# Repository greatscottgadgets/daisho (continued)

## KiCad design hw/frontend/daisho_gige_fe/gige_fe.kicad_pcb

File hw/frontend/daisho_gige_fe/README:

Copyright 2014 Mike Kershaw, Michael Ossmann

These files are part of HackRF.

This is a free hardware design; you can redistribute it and/or modify
it under the terms of the GNU General Public License as published by
the Free Software Foundation; either version 2, or (at your option)
any later version.

This design is distributed in the hope that it will be useful,
but WITHOUT ANY WARRANTY; without even the implied warranty of
MERCHANTABILITY or FITNESS FOR A PARTICULAR PURPOSE.  See the
GNU General Public License for more details.

You should have received a copy of the GNU General Public License
along with this design; see the file COPYING.  If not, write to
the Free Software Foundation, Inc., 51 Franklin Street,
Boston, MA 02110-1301, USA.

hardware notes:

Schematic and layout files were designed in KiCad, an open source electronic
design automation package.

order of copper layers:
    Copper 1:  C1F (front)
    Copper 2:  C2
    Copper 3:  C3
    Copper 4:  C1B (back)

PCB description: 4 layer PCB 0.0646 in
    Copper       1:  1 oz copper (1.4 mil)
    Dielectric 1-2:  6.7 mil prepreg
    Copper       2:  0.5 oz copper (0.7 mil)
    Dielectric 2-3:  47 mil core
    Copper       3:  0.5 oz copper (0.7 mil)
    Dielectric 3-4:  6.7 mil prepreg
    Copper       4:  1 oz copper (1.4 mil)

FR408 or similar substrate with Er=3.66 (+/- 0.1)
double side solder mask green
double side silkscreen white
6 mil min trace width and
6 mil min isolation
10 mil min drill

PCBs of this specification are available from OSH Park.

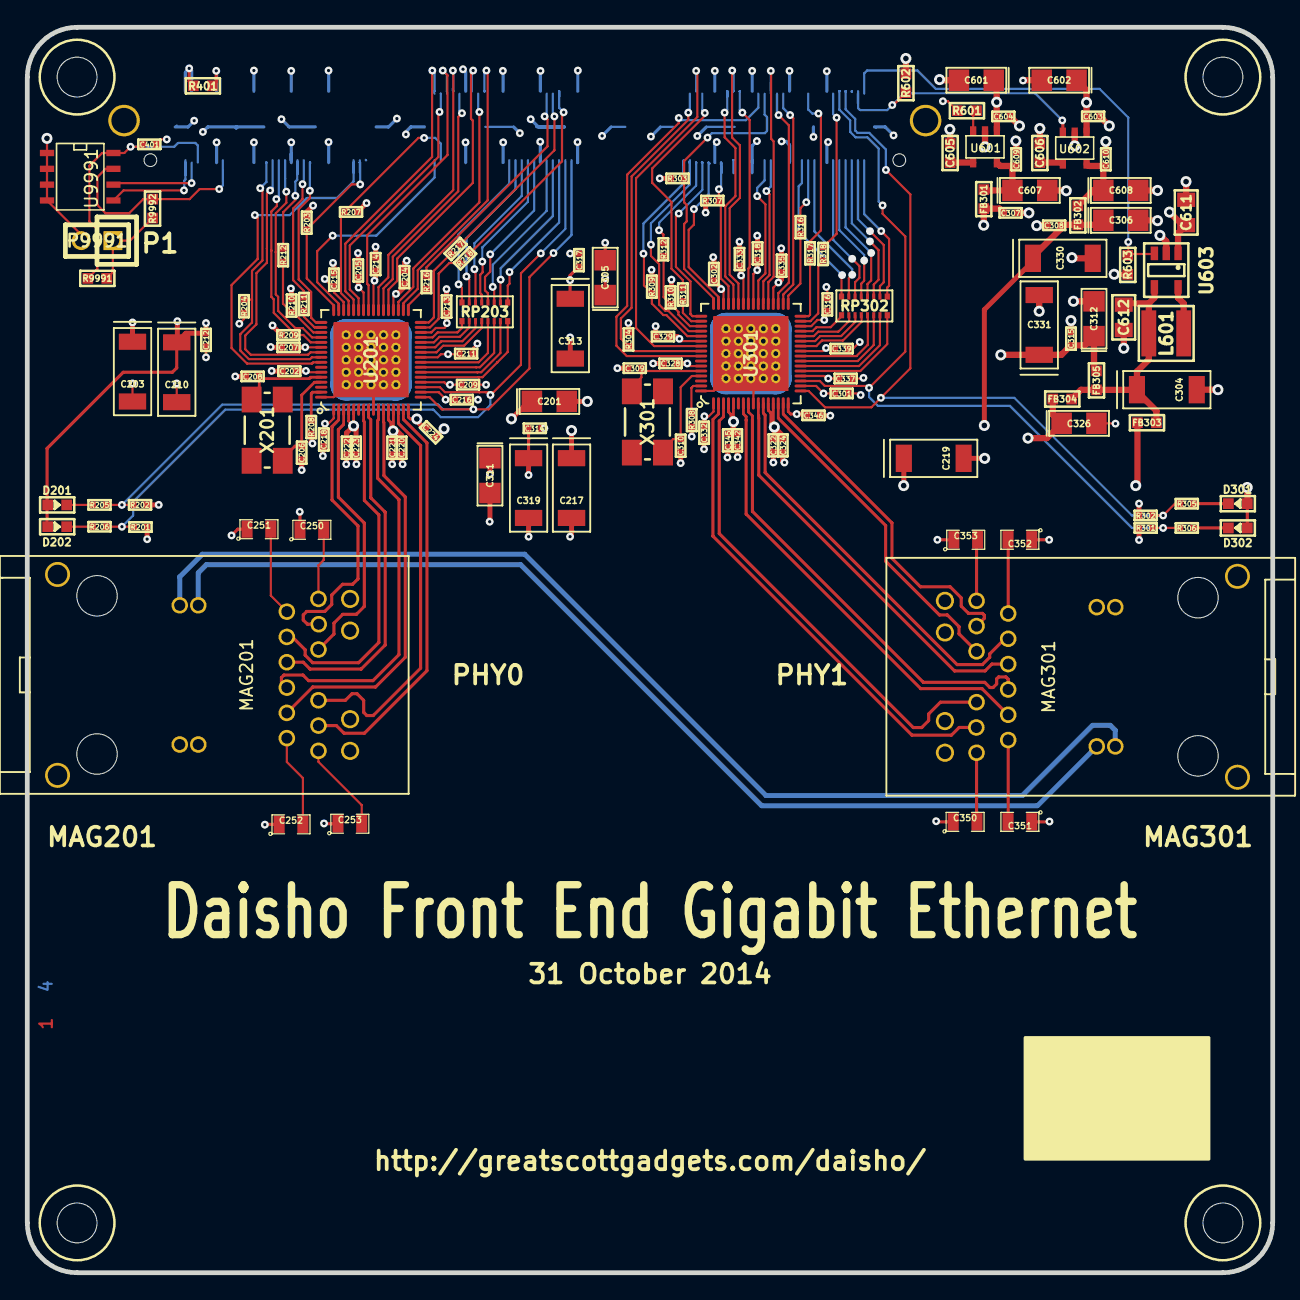
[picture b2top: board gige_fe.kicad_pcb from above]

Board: 4 copper layers, 100.0 x 100.0 mm, 142 parts (0 on the bottom side), 150 nets.

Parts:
C201, C305, C306, C311, C312, C326, C601, C602, C607, C608: 10uF; gsg-sm1206p
C202, C307, C308, C314, C315, C328, C401, C603, C604, C609, C610: 0.1uF; GSG-0402
C203, C210, C217, C219: 47uF; GSG-2312
C204, C205, C207, C209, C211, C212, C213, C214, C215, C216, C218, C220, C221, C222, C223, C224, C301, C302, C316, C317, C318, C322, C324, C329, C332, C333, C335, C337, C339, C342, C345, C346: 10nF; GSG-0402
C206, C208, C309, C310: 22pF; GSG-0402
C250, C251, C252, C253, C350, C351, C352, C353: 0.1uF; SM0805
C304, C313, C319, C330, C331: 47uF; gsg-2312
C605, C606: 470pF; GSG-0603
C611, C612: 10uF; GSG-0805
D201: PHY0_ACT; GSG-0603D
D202: PHY0_LNK; GSG-0603D
D301: PHY1_ACT_YEL; GSG-0603D
D302: PHY1_LNK_GREEN; GSG-0603D
FB301, FB302, FB303, FB304, FB305: FBEAD; GSG-0603
H1, H2, H3, H4: HOLE; GSG-HOLE126MIL
J9991: SAMTEC_QSH-090-D; SAMTEC_QSH-090-01-F-D-A
L601: 4u7; GSG-NRG4026
MAG201, MAG301: BELFUSE-0826-1X1T-M1-F; BELFUSE-MAG
P9991: CONN_2; GSG-HEADER-1x2
R201, R202, R203, R205, R206, R207, R301, R302, R303, R305, R306, R307: 1k; GSG-0402
R204, R209, R210, R304, R309, R310: 4.7K; GSG-0402
R208, R308: 12.1k 1%; GSG-0402
R211, R212, R216, R217, R218, R311, R312, R316, R317, R318: 0; GSG-0402
R401, R601, R602, R603, R9991, R9992: 10k; GSG-0603
RP203, RP302: 0; 1506-RPACK
U201, U301: KSZ9031MNX; GSG-QFN64-25
U601: MIC5207-2.5YM5; SOT23-5
U602: MIC5207-3.3YM5; SOT23-5
U603: XC9236-MR; IPC_SOT95P280X110-5N
U9991: 24C08; SO8E
X201, X301: 25MHz; ABMM2

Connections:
/Board Power/V2P5_EN: R601.1, U601.3
/GigE Phy0/GTX_CLK: R217.1, U201.32
/GigE Phy0/LED1_D: D202.2, R206.1
/GigE Phy0/LED2_D: D201.2, R205.1
/GigE Phy0/TXD0: RP203.8, U201.21
/GigE Phy0/TXD1: RP203.7, U201.22
/GigE Phy0/TXD2: RP203.6, U201.23
/GigE Phy0/TXD3: RP203.5, U201.24
/GigE Phy0/TXD4: RP203.4, U201.26
/GigE Phy0/TXD5: RP203.3, U201.27
/GigE Phy0/TXD6: RP203.2, U201.28
/GigE Phy0/TXD7: RP203.1, U201.29
/GigE Phy1/GTX_CLK: R317.1, U301.32
/GigE Phy1/LED1_D: D302.2, R306.1
/GigE Phy1/LED2_D: D301.2, R305.1
/GigE Phy1/TXD0: RP302.8, U301.21
/GigE Phy1/TXD1: RP302.7, U301.22
/GigE Phy1/TXD2: RP302.6, U301.23
/GigE Phy1/TXD3: RP302.5, U301.24
/GigE Phy1/TXD4: RP302.4, U301.26
/GigE Phy1/TXD5: RP302.3, U301.27
/GigE Phy1/TXD6: RP302.2, U301.28
/GigE Phy1/TXD7: RP302.1, U301.29
/daisho connector/FE_I2C_SCL: J9991.4, U9991.6
/daisho connector/FE_I2C_SDA: J9991.2, U9991.5
/daisho connector/VALT_FE: J9991.1, J9991.3, R401.1
FE_I2C_EEPROM_WP: J9991.14, R9992.1, U9991.7
FE_I2C_VCC: C401.1, J9991.6, R9991.1, U9991.8
GIGE_AVDDH: C217.1, C218.1, C224.1, C306.1, C308.1, C330.1, C332.1, C346.1, FB302.2, U201.1, U201.16, U301.1, U301.16
GIGE_AVDDL: C219.1, C220.1, C221.1, C222.1, C223.1, C311.1, C314.1, C319.1, C322.1, C324.1, C342.1, C345.1, FB303.2, U201.4, U201.5, U201.12, U201.13, U301.4, U301.5, U301.12, U301.13
GIGE_AVDD_PLL: C201.1, C202.1, C326.1, C328.1, FB304.2, U201.59, U301.59
GIGE_DVDDH: C210.1, C212.1, C213.1, C214.1, C215.1, C216.1, C301.1, C302.1, C305.1, C307.1, C313.1, C316.1, C317.1, C318.1, D201.1, D202.1, D301.1, D302.1, FB301.2, J9991.12, J9991.24, J9991.36, J9991.48, J9991.71, J9991.72, J9991.83, J9991.84, J9991.95, J9991.96, J9991.107, J9991.108, J9991.131, J9991.132, J9991.143, J9991.144, J9991.155, J9991.156, J9991.167, J9991.168, R209.2, R210.1, R309.1, R310.1, U201.18, U201.30, U201.40, U201.46, U301.18, U301.30, U301.40, U301.46
GIGE_DVDDL: C203.1, C204.1, C205.1, C207.1, C209.1, C211.1, C312.1, C315.1, C329.1, C331.1, C333.1, C335.1, C337.1, C339.1, FB305.2, U201.20, U201.25, U201.36, U201.42, U201.54, U301.20, U301.25, U301.36, U301.42, U301.54
GND: C201.2, C202.2, C203.2, C204.2, C205.2, C206.1, C207.2, C208.1, C209.2, C210.2, C211.2, C212.2, C213.2, C214.2, C215.2, C216.2, C217.2, C218.2, C219.2, C220.2, C221.2, C222.2, C223.2, C224.2, C250.1, C251.1, C252.1, C253.1, C301.2, C302.2, C304.2, C305.2, C306.2, C307.2, C308.2, C309.1, C310.1, C311.2, C312.2, C313.2, C314.2, C315.2, C316.2, C317.2, C318.2, C319.2, C322.2, C324.2, C326.2, C328.2, C329.2, C330.2, C331.2, C332.2, C333.2, C335.2, C337.2, C339.2, C342.2, C345.2, C346.2, C350.1, C351.1, C352.1, C353.1, C401.2, C601.2, C602.2, C603.2, C604.2, C605.2, C606.2, C607.2, C608.2, C609.2, C610.2, C611.1, C612.2, J9991.A0, J9991.A1, J9991.A2, J9991.A3, J9991.B0, J9991.B1, J9991.B2, J9991.B3, J9991.C0, J9991.C1, J9991.C2, J9991.C3, P9991.2, R201.2, R202.2, R203.2, R204.2, R207.2, R208.1, R301.2, R302.2, R303.2, R304.2, R307.2, R308.1, R602.2, R603.2, U201.0, U201.9, U201.64, U301.0, U301.9, U301.64, U601.2, U602.2, U603.2, U9991.1, U9991.2, U9991.3, U9991.4
MAG_VC_1: MAG201.13, MAG301.13
MAG_VC_2: MAG201.14, MAG301.14
MAG_VC_3: MAG201.15, MAG301.15
MAG_VC_4: MAG201.16, MAG301.16
unnamed: C206.2, U201.61, X201.1
unnamed: C208.2, U201.60, X201.2
unnamed: C250.2, MAG201.12
unnamed: C251.2, MAG201.6
unnamed: C252.2, MAG201.1
unnamed: C253.2, MAG201.7
unnamed: C309.2, U301.60, X301.2
unnamed: C310.2, U301.61, X301.1
unnamed: C350.2, MAG301.12
unnamed: C351.2, MAG301.6
unnamed: C352.2, MAG301.1
unnamed: C353.2, MAG301.7
unnamed: C605.1, U601.4
unnamed: C606.1, U602.4
unnamed: L601.1, U603.5
unnamed: P9991.1, R9991.2, R9992.2
unnamed: R208.2, U201.63
unnamed: R308.2, U301.63
PHY0_CLK125_NDO: J9991.30, U201.55
PHY0_COL: J9991.34, U201.52
PHY0_CRS: J9991.42, U201.49
PHY0_GM_GTX_CLK: J9991.99, R217.2
PHY0_GM_MDC: J9991.40, R211.2
PHY0_GM_MIO: J9991.38, R212.2
PHY0_GM_RXD0: J9991.61, U201.44
PHY0_GM_RXD1: J9991.63, U201.43
PHY0_GM_RXD2: J9991.65, U201.41
PHY0_GM_RXD3: J9991.67, U201.39
PHY0_GM_RXD4: J9991.69, U201.38
PHY0_GM_RXD5: J9991.73, U201.37
PHY0_GM_RXD6: J9991.75, U201.35
PHY0_GM_RXD7: J9991.77, U201.34
PHY0_GM_RX_CLK: J9991.58, R203.1, U201.48
PHY0_GM_RX_ERR: J9991.62, U201.47
PHY0_GM_TXD0: J9991.102, RP203.9
PHY0_GM_TXD1: J9991.100, RP203.10
PHY0_GM_TXD2: J9991.98, RP203.11
PHY0_GM_TXD3: J9991.94, RP203.12
PHY0_GM_TXD4: J9991.92, RP203.13
PHY0_GM_TXD5: J9991.90, RP203.14
PHY0_GM_TXD6: J9991.88, RP203.15
PHY0_GM_TXD7: J9991.86, RP203.16
PHY0_GM_TX_EN: J9991.97, R216.2
PHY0_GM_TX_ER: J9991.101, R218.2
PHY0_HW_RST: J9991.28, R204.1, U201.56
PHY0_INT_N: J9991.32, R209.1, U201.53
PHY0_MDC: R211.1, U201.50
PHY0_MDIO: R210.2, R212.1, U201.51
PHY0_PHYADDR0: J9991.104, R201.1, R206.2, U201.19
PHY0_PHYADDR1: J9991.106, R202.1, R205.2, U201.17
PHY0_RXDV: J9991.64, R207.1, U201.45
PHY0_TXRXM_A: MAG201.10, U201.3
PHY0_TXRXM_B: MAG201.4, U201.8
PHY0_TXRXM_C: MAG201.2, U201.11
PHY0_TXRXM_D: MAG201.8, U201.15
PHY0_TXRXP_A: MAG201.11, U201.2
PHY0_TXRXP_B: MAG201.5, U201.7
PHY0_TXRXP_C: MAG201.3, U201.10
PHY0_TXRXP_D: MAG201.9, U201.14
PHY0_TX_CLK: J9991.56, U201.57
PHY0_TX_EN: R216.1, U201.33
PHY0_TX_ER: R218.1, U201.31
PHY1_CLK125_NDO: J9991.125, U301.55
PHY1_COL: J9991.124, U301.52
PHY1_CRS: J9991.128, U301.49
PHY1_GM_GTX_CLK: J9991.161, R317.2
PHY1_GM_MDC: J9991.127, R311.2
PHY1_GM_MIO: J9991.126, R312.2
PHY1_GM_RXD0: J9991.135, U301.44
PHY1_GM_RXD1: J9991.137, U301.43
PHY1_GM_RXD2: J9991.139, U301.41
PHY1_GM_RXD3: J9991.148, U301.39
PHY1_GM_RXD4: J9991.150, U301.38
PHY1_GM_RXD5: J9991.149, U301.37
PHY1_GM_RXD6: J9991.151, U301.35
PHY1_GM_RXD7: J9991.153, U301.34
PHY1_GM_RXDV: J9991.134, R307.1, U301.45
PHY1_GM_RX_CLK: J9991.147, R303.1, U301.48
PHY1_GM_RX_ERR: J9991.130, U301.47
PHY1_GM_TXD0: J9991.180, RP302.9
PHY1_GM_TXD1: J9991.178, RP302.10
PHY1_GM_TXD2: J9991.176, RP302.11
PHY1_GM_TXD3: J9991.174, RP302.12
PHY1_GM_TXD4: J9991.172, RP302.13
PHY1_GM_TXD5: J9991.170, RP302.14
PHY1_GM_TXD6: J9991.164, RP302.15
PHY1_GM_TXD7: J9991.160, RP302.16
PHY1_GM_TX_EN: J9991.162, R316.2
PHY1_GM_TX_ER: J9991.169, R318.2
PHY1_HW_RST: J9991.123, R304.1, U301.56
PHY1_INT_N: J9991.122, R309.2, U301.53
PHY1_MDC: R311.1, U301.50
PHY1_MDIO: R310.2, R312.1, U301.51
PHY1_PHYADDR0: J9991.171, R301.1, R306.2, U301.19
PHY1_PHYADDR1: J9991.173, R302.1, R305.2, U301.17
PHY1_TXRXM_A: MAG301.10, U301.3
PHY1_TXRXM_B: MAG301.4, U301.8
PHY1_TXRXM_C: MAG301.2, U301.11
PHY1_TXRXM_D: MAG301.8, U301.15
PHY1_TXRXP_A: MAG301.11, U301.2
PHY1_TXRXP_B: MAG301.5, U301.7
PHY1_TXRXP_C: MAG301.3, U301.10
PHY1_TXRXP_D: MAG301.9, U301.14
PHY1_TX_CLK: J9991.145, U301.57
PHY1_TX_EN: R316.1, U301.33
PHY1_TX_ER: R318.1, U301.31
V1P2_EN: J9991.179, R603.1, U603.3
V1P2_REG: C304.1, C612.1, FB303.1, FB304.1, FB305.1, L601.2, U603.4
V2P5_REG: C607.1, C609.1, FB301.1, U601.5
V3P3_EN: J9991.177, R602.1, U602.3
V3P3_REG: C608.1, C610.1, FB302.1, U602.5
VRAW_SW_5V: C601.1, C602.1, C603.1, C604.1, C611.2, J9991.11, J9991.23, J9991.35, J9991.47, R401.2, R601.2, U601.1, U602.1, U603.1

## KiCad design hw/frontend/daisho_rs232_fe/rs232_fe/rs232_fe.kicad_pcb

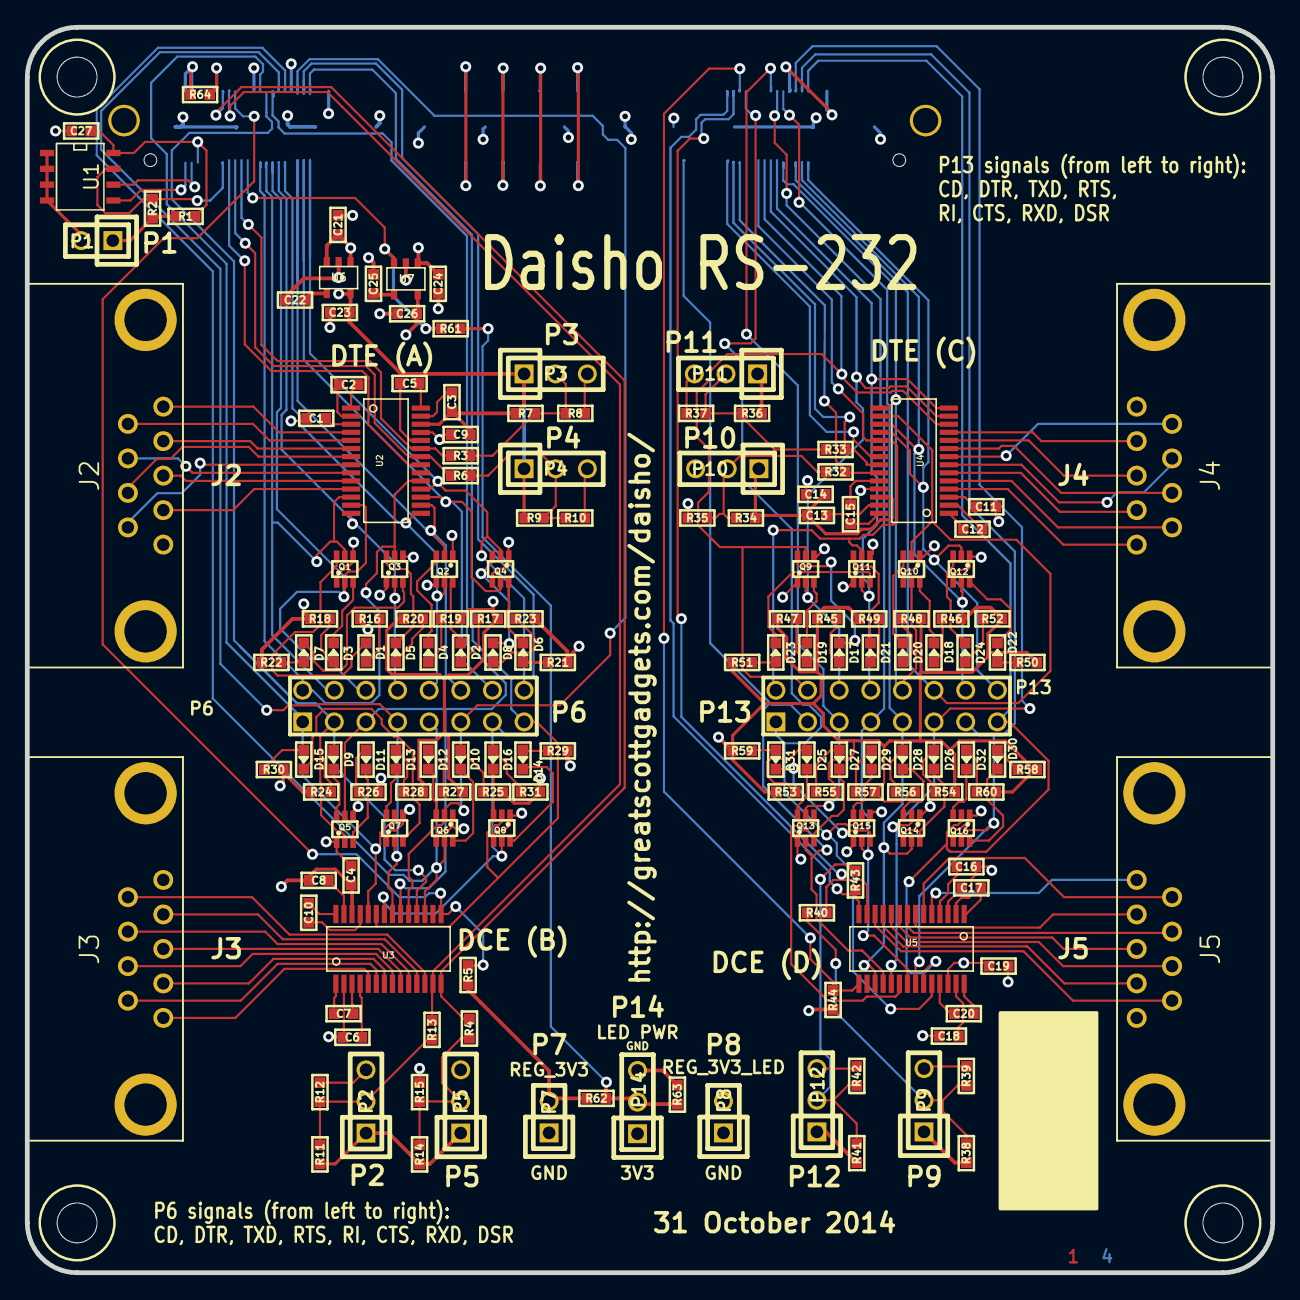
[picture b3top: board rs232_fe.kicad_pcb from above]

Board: 4 copper layers, 100.0 x 100.0 mm, 169 parts (1 on the bottom side), 186 nets.

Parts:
C1, C2, C3, C4, C5, C6, C7, C8, C9, C10, C11, C12, C13, C14, C15, C16, C17, C18, C19, C20, C27: 0.1uF; GSG-0603
C21, C23, C24, C26: 1uF; GSG-0603
C22, C25: 100nF; GSG-0603
D1, D2, D3, D4, D5, D6, D7, D8, D9, D10, D11, D12, D13, D14, D15, D16, D17, D18, D19, D20, D21, D22, D23, D24, D25, D26, D27, D28, D29, D30, D31, D32: LED; GSG-0603D
H1, H2, H3, H4: HOLE; GSG-HOLE126MIL
J1: SAMTEC_QSH-090-D; SAMTEC_QSH-090-01-F-D-A
J2, J4: DB9; SDS107-PRW1-M09-SN63-11
J3, J5: DB9; SDS107-PRP2-F09-SN13-11
P1, P7, P8: CONN_2; GSG-HEADER-1x2
P2, P3, P4, P5, P9, P10, P11, P12, P14: CONN_3; GSG-HEADER-1x3
P6, P13: CONN_8X2; pin_array_8x2
Q1, Q2, Q3, Q4, Q5, Q6, Q7, Q8, Q9, Q10, Q11, Q12, Q13, Q14, Q15, Q16: MUN5212DW1; GSG-SOT363
R1, R2, R3, R6, R7, R8, R9, R10, R11, R12, R14, R15, R32, R33, R34, R35, R36, R37, R38, R39, R41, R42, R61, R62, R63, R64: 10k; GSG-0603
R4, R5, R13, R40, R43, R44: 10K; GSG-0603
R16, R17, R18, R19, R20, R21, R22, R23, R24, R25, R26, R27, R28, R29, R30, R31, R45, R46, R47, R48, R49, R50, R51, R52, R53, R54, R55, R56, R57, R58, R59, R60: 470; GSG-0603
U1: 24C08; SO8E
U2, U4: TRSF3243; tssop-28
U3, U5: TRS3237E; tssop-28
U6, U7: MIC5318; SOT23-5

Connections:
!EN-B-TTL: J1.15, R13.1, U3.13
!EN-D-TTL: J1.137, R40.1, U5.13
!FORCEOFF-A-TTL: J1.18, R6.1, U2.22
!FORCEOFF-C-TTL: J1.138, R33.1, U4.22
!INVALID-A-TTL: J1.16, U2.21
!INVALID-C-TTL: J1.136, U4.21
!SHDN-B-TTL: J1.13, R4.1, U3.14
!SHDN-D-TTL: J1.135, R43.1, U5.14
/daisho_connector/FE_I2C_SCL: J1.4, U1.6
/daisho_connector/FE_I2C_SDA: J1.2, U1.5
/daisho_connector/VALT_FE: J1.1, J1.3, R64.2
/daisho_connector/VRAW_SW_5V: C21.1, C24.1, J1.11, J1.23, J1.35, J1.47, R64.1, U6.1, U6.3, U7.1
/rs232_pair_AB/CD-A-232: J2.1, U2.4
/rs232_pair_AB/CD-B-232: J3.1, U3.5
/rs232_pair_AB/CTS-A-232: J2.8, U2.7
/rs232_pair_AB/CTS-B-232: J3.8, U3.10
/rs232_pair_AB/DSR-A-232: J2.6, U2.5
/rs232_pair_AB/DSR-B-232: J3.6, U3.6
/rs232_pair_AB/DTR-A-232: J2.4, U2.11
/rs232_pair_AB/DTR-B-232: J3.4, U3.11
/rs232_pair_AB/RI-A-232: J2.9, U2.8
/rs232_pair_AB/RI-B-232: J3.9, U3.12
/rs232_pair_AB/RTS-A-232: J2.7, U2.9
/rs232_pair_AB/RTS-B-232: J3.7, U3.8
/rs232_pair_AB/RXD-A-232: J2.2, U2.6
/rs232_pair_AB/RXD-B-232: J3.2, U3.7
/rs232_pair_AB/TXD-A-232: J2.3, U2.10
/rs232_pair_AB/TXD-B-232: J3.3, U3.9
/rs232_pair_CD/CD-C-232: J4.1, U4.4
/rs232_pair_CD/CD-D-232: J5.1, U5.5
/rs232_pair_CD/CTS-C-232: J4.8, U4.7
/rs232_pair_CD/CTS-D-232: J5.8, U5.10
/rs232_pair_CD/DSR-C-232: J4.6, U4.5
/rs232_pair_CD/DSR-D-232: J5.6, U5.6
/rs232_pair_CD/DTR-C-232: J4.4, U4.11
/rs232_pair_CD/DTR-D-232: J5.4, U5.11
/rs232_pair_CD/RI-C-232: J4.9, U4.8
/rs232_pair_CD/RI-D-232: J5.9, U5.12
/rs232_pair_CD/RTS-C-232: J4.7, U4.9
/rs232_pair_CD/RTS-D-232: J5.7, U5.8
/rs232_pair_CD/RXD-C-232: J4.2, U4.6
/rs232_pair_CD/RXD-D-232: J5.2, U5.7
/rs232_pair_CD/TXD-C-232: J4.3, U4.10
/rs232_pair_CD/TXD-D-232: J5.3, U5.9
CD-A-TTL: J1.26, P6.2, Q3.5, U2.19
CD-B-TTL: J1.25, P6.1, Q7.5, U3.24
CD-C-TTL: J1.146, P13.2, Q11.5, U4.19
CD-D-TTL: J1.141, P13.1, Q15.5, U5.24
CTS-A-TTL: J1.38, P6.12, Q2.2, U2.16
CTS-B-TTL: J1.37, P6.11, Q6.2, U3.19
CTS-C-TTL: J1.158, P13.12, Q10.2, U4.16
CTS-D-TTL: J1.157, P13.11, Q14.2, U5.19
DSR-A-TTL: J1.42, P6.16, Q4.2, U2.18
DSR-B-TTL: J1.41, P6.15, Q8.2, U3.23
DSR-C-TTL: J1.162, P13.16, Q12.2, U4.18
DSR-D-TTL: J1.161, P13.15, Q16.2, U5.23
DTR-A-TTL: J1.28, P6.4, Q1.5, U2.12
DTR-B-TTL: J1.27, P6.3, Q5.2, U3.18
DTR-C-TTL: J1.148, P13.4, Q9.5, U4.12
DTR-D-TTL: J1.122, P13.3, Q13.2, U5.18
FE_I2C_EEPROM_WP: J1.14, R2.1, U1.7
FE_I2C_VCC: C27.1, J1.6, R1.1, U1.8
FORCEON-A-TTL: J1.20, R3.1, U2.23
FORCEON-C-TTL: J1.140, R32.1, U4.23
GND: C1.2, C4.2, C6.2, C9.2, C11.2, C14.2, C16.2, C19.2, C21.2, C22.2, C23.2, C24.2, C25.2, C26.2, C27.2, J1.A0, J1.A1, J1.A2, J1.A3, J1.B0, J1.B1, J1.B2, J1.B3, J1.C0, J1.C1, J1.C2, J1.C3, J2.5, J3.5, J4.5, J5.5, P1.2, P2.3, P3.3, P4.3, P5.3, P7.1, P8.1, P9.3, P10.3, P11.3, P12.3, P14.3, Q1.1, Q1.4, Q2.1, Q2.4, Q3.1, Q3.4, Q4.1, Q4.4, Q5.1, Q5.4, Q6.1, Q6.4, Q7.1, Q7.4, Q8.1, Q8.4, Q9.1, Q9.4, Q10.1, Q10.4, Q11.1, Q11.4, Q12.1, Q12.4, Q13.1, Q13.4, Q14.1, Q14.4, Q15.1, Q15.4, Q16.1, Q16.4, R8.2, R10.2, R12.2, R15.2, R35.2, R37.2, R39.2, R42.2, R63.2, U1.1, U1.2, U1.3, U1.4, U2.25, U3.2, U4.25, U5.2, U6.2, U7.2
LEDS_PWR: J1.22, R61.1, U7.3
MBAUD-B-TTL: J1.17, R5.1, U3.15
MBAUD-D-TTL: J1.139, R44.1, U5.15
unnamed: C1.1, U2.3
unnamed: C2.1, U2.1
unnamed: C2.2, U2.2
unnamed: C3.1, U2.27
unnamed: C5.1, U2.24
unnamed: C5.2, U2.28
unnamed: C6.1, U3.4
unnamed: C7.1, U3.1
unnamed: C7.2, U3.3
unnamed: C8.2, U3.27
unnamed: C10.1, U3.28
unnamed: C10.2, U3.25
unnamed: C11.1, U4.3
unnamed: C12.1, U4.1
unnamed: C12.2, U4.2
unnamed: C13.1, U4.27
unnamed: C15.1, U4.24
unnamed: C15.2, U4.28
unnamed: C16.1, U5.4
unnamed: C17.1, U5.1
unnamed: C17.2, U5.3
unnamed: C18.2, U5.27
unnamed: C20.1, U5.28
unnamed: C20.2, U5.25
unnamed: C22.1, U6.4
unnamed: C25.1, U7.4
unnamed: D1.1, R16.1
unnamed: D1.2, Q1.6
unnamed: D2.1, R17.1
unnamed: D2.2, Q2.6
unnamed: D3.1, R18.1
unnamed: D3.2, Q1.3
unnamed: D4.1, R19.1
unnamed: D4.2, Q2.3
unnamed: D5.1, R20.1
unnamed: D5.2, Q3.6
unnamed: D6.1, R21.1
unnamed: D6.2, Q4.6
unnamed: D7.1, R22.1
unnamed: D7.2, Q3.3
unnamed: D8.1, R23.1
unnamed: D8.2, Q4.3
unnamed: D9.1, R24.1
unnamed: D9.2, Q5.6
unnamed: D10.1, R25.1
unnamed: D10.2, Q6.6
unnamed: D11.1, R26.1
unnamed: D11.2, Q5.3
unnamed: D12.1, R27.1
unnamed: D12.2, Q6.3
unnamed: D13.1, R28.1
unnamed: D13.2, Q7.6
unnamed: D14.1, R29.1
unnamed: D14.2, Q8.6
unnamed: D15.1, R30.1
unnamed: D15.2, Q7.3
unnamed: D16.1, R31.1
unnamed: D16.2, Q8.3
unnamed: D17.1, R45.1
unnamed: D17.2, Q9.6
unnamed: D18.1, R46.1
unnamed: D18.2, Q10.6
unnamed: D19.1, R47.1
unnamed: D19.2, Q9.3
unnamed: D20.1, R48.1
unnamed: D20.2, Q10.3
unnamed: D21.1, R49.1
unnamed: D21.2, Q11.6
unnamed: D22.1, R50.1
unnamed: D22.2, Q12.6
unnamed: D23.1, R51.1
unnamed: D23.2, Q11.3
unnamed: D24.1, R52.1
unnamed: D24.2, Q12.3
unnamed: D25.1, R53.1
unnamed: D25.2, Q13.6
unnamed: D26.1, R54.1
unnamed: D26.2, Q14.6
unnamed: D27.1, R55.1
unnamed: D27.2, Q13.3
unnamed: D28.1, R56.1
unnamed: D28.2, Q14.3
unnamed: D29.1, R57.1
unnamed: D29.2, Q15.6
unnamed: D30.1, R58.1
unnamed: D30.2, Q16.6
unnamed: D31.1, R59.1
unnamed: D31.2, Q15.3
unnamed: D32.1, R60.1
unnamed: D32.2, Q16.3
unnamed: P1.1, R1.2, R2.2
unnamed: P2.2, R11.2, R12.1, R13.2
unnamed: P3.2, R3.2, R7.2, R8.1
unnamed: P4.2, R6.2, R9.2, R10.1
unnamed: P5.2, R4.2, R14.2, R15.1
unnamed: P9.2, R38.2, R39.1, R40.2
unnamed: P10.2, R32.2, R34.2, R35.1
unnamed: P11.2, R33.2, R36.2, R37.1
unnamed: P12.2, R41.2, R42.1, R43.2
unnamed: P14.2, R61.2, R62.2, R63.1
REG_3V3: C3.2, C4.1, C8.1, C9.1, C13.2, C14.1, C18.1, C19.1, C23.1, J1.12, J1.24, J1.36, J1.48, J1.71, J1.72, J1.83, J1.84, J1.95, J1.96, J1.107, J1.108, J1.131, J1.132, J1.143, J1.144, J1.155, J1.156, J1.167, J1.168, P2.1, P3.1, P4.1, P5.1, P7.2, P9.1, P10.1, P11.1, P12.1, P14.1, R5.2, R7.1, R9.1, R11.1, R14.1, R34.1, R36.1, R38.1, R41.1, R44.2, R62.1, U2.26, U3.26, U4.26, U5.26, U6.5
REG_3V3_LED: C26.1, P8.2, R16.2, R17.2, R18.2, R19.2, R20.2, R21.2, R22.2, R23.2, R24.2, R25.2, R26.2, R27.2, R28.2, R29.2, R30.2, R31.2, R45.2, R46.2, R47.2, R48.2, R49.2, R50.2, R51.2, R52.2, R53.2, R54.2, R55.2, R56.2, R57.2, R58.2, R59.2, R60.2, U7.5
RI-A-TTL: J1.34, P6.10, Q2.5, U2.15
RI-B-TTL: J1.33, P6.9, Q6.5, U3.17
RI-C-TTL: J1.154, P13.10, Q10.5, U4.15
RI-D-TTL: J1.153, P13.9, Q14.5, U5.17
RTS-A-TTL: J1.32, P6.8, Q3.2, U2.14
RTS-B-TTL: J1.31, P6.7, Q7.2, U3.21
RTS-C-TTL: J1.152, P13.8, Q11.2, U4.14
RTS-D-TTL: J1.151, P13.7, Q15.2, U5.21
RXD-A-TTL: J1.40, P6.14, Q4.5, U2.17
RXD-B-TTL: J1.39, P6.13, Q8.5, U3.22
RXD-C-TTL: J1.160, P13.14, Q12.5, U4.17
RXD-D-TTL: J1.159, P13.13, Q16.5, U5.22
TXD-A-TTL: J1.30, P6.6, Q1.2, U2.13
TXD-B-TTL: J1.29, P6.5, Q5.5, U3.20
TXD-C-TTL: J1.150, P13.6, Q9.2, U4.13
TXD-D-TTL: J1.149, P13.5, Q13.5, U5.20
